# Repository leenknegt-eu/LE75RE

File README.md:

75 key, ortholinear, wired, 60% hot swappable keyboard for MX style (RE, RGB) and Gateron KS-33 low profile switches (LRE, LRGB).
Inspired by the Xiudi XD75RE which does not appear to be in regular production anymore.
All variants should be plate and case compatible with the XD75.
The legacy versions are ATMega32 powered and are pin for pin compatible with the XD75 and should be able to use the same firmware.
The LE75RGB variants have per-key RGB backlighting intended for use with SK6803MINI-E LED ICs.

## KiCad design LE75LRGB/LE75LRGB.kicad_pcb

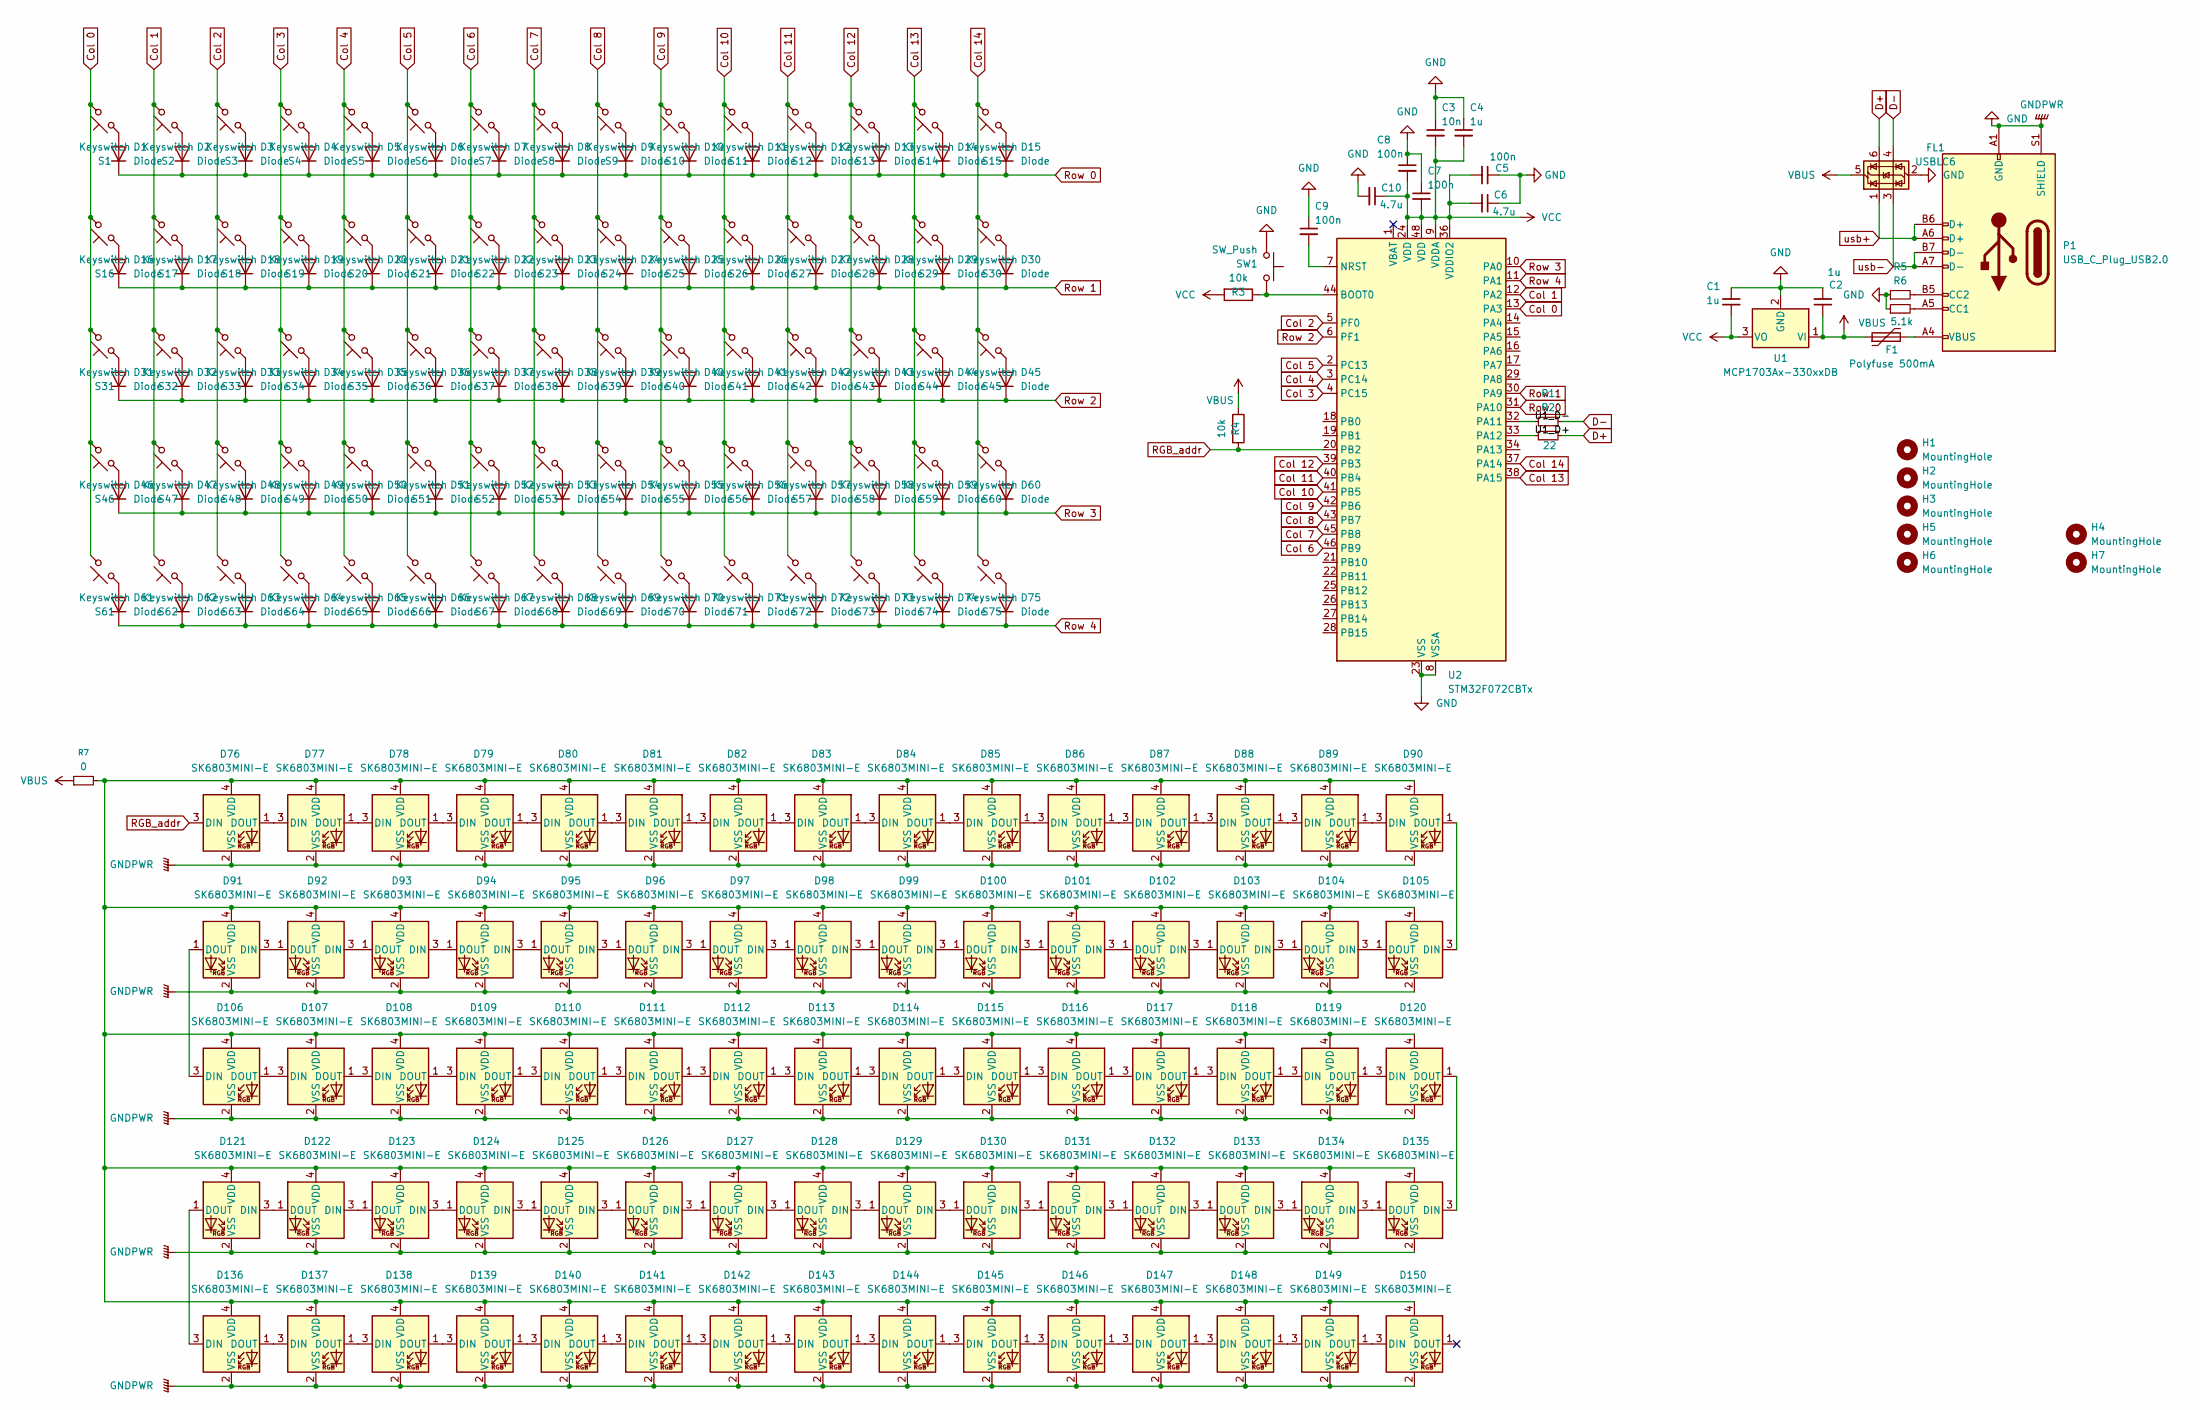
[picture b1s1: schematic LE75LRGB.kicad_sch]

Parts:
C1, C2, C4: 1u; C_0603_1608Metric
C3: 10n; C_0603_1608Metric
C5, C7, C8, C9: 100n; C_0603_1608Metric
C6, C10: 4.7u; C_0603_1608Metric
D1, D2, D3, D4, D5, D6, D7, D8, D9, D10, D11, D12, D13, D14, D15, D16, D17, D18, D19, D20, D21, D22, D23, D24, D25, D26, D27, D28, D29, D30, D31, D32, D33, D34, D35, D36, D37, D38, D39, D40, D41, D42, D43, D44, D45, D46, D47, D48, D49, D50, D51, D52, D53, D54, D55, D56, D57, D58, D59, D60, D61, D62, D63, D64, D65, D66, D67, D68, D69, D70, D71, D72, D73, D74, D75: Diode; D_0805_2012Metric
D76, D77, D78, D79, D80, D81, D82, D83, D84, D85, D86, D87, D88, D89, D90, D91, D92, D93, D94, D95, D96, D97, D98, D99, D100, D101, D102, D103, D104, D105, D106, D107, D108, D109, D110, D111, D112, D113, D114, D115, D116, D117, D118, D119, D120, D121, D122, D123, D124, D125, D126, D127, D128, D129, D130, D131, D132, D133, D134, D135, D136, D137, D138, D139, D140, D141, D142, D143, D144, D145, D146, D147, D148, D149, D150: SK6803MINI-E; SK6812-MINI-E
F1: Polyfuse 500mA; Fuse_1206_3216Metric
FL1: USBLC6; SOT-23-6; Manufacturer_Part_Number ECMF02-4CMX8; Mouser Part Number 511-ECMF02-4CMX8
H1, H2, H3, H5, H6: MountingHole; MountingHole_2.7mm_M2.5_ISO7380
H4, H7: MountingHole; MountingSlot_2.7mm_M2.5_ISO7380
P1: USB_C_Plug_USB2.0; USB_C_Receptacle_Palconn_UTC16-G
R1, R2: 22; R_0603_1608Metric
R3, R4: 10k; R_0603_1608Metric
R5, R6: 5.1k; R_0603_1608Metric
R7: 0; C_0603_1608Metric
S1, S2, S3, S4, S5, S6, S7, S8, S9, S10, S11, S12, S13, S14, S15, S16, S17, S18, S19, S20, S21, S22, S23, S24, S25, S26, S27, S28, S29, S30, S31, S32, S33, S34, S35, S36, S37, S38, S39, S40, S41, S42, S43, S44, S45, S46, S47, S48, S49, S50, S51, S52, S53, S54, S55, S56, S57, S58, S59, S60, S61, S62, S63, S64, S65, S66, S67, S68, S69, S70, S71, S72, S73, S74, S75: Keyswitch; Gateron-KS33-Hotswap-1U
SW1: SW_Push; SW_SPST_TL3342
U1: MCP1703Ax-330xxDB; SOT-23
U2: STM32F072CBTx; LQFP-48_7x7mm_P0.5mm

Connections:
/U1_D+: R2.1, U2.33 (PA12)
/U1_D-: R1.1, U2.32 (PA11)
Col 0: S1.2, S16.2, S31.2, S46.2, S61.2, U2.13 (PA3)
Col 1: S2.2, S17.2, S32.2, S47.2, S62.2, U2.12 (PA2)
Col 2: S3.2, S18.2, S33.2, S48.2, S63.2, U2.5 (PF0)
Col 3: S4.2, S19.2, S34.2, S49.2, S64.2, U2.4 (PC15)
Col 4: S5.2, S20.2, S35.2, S50.2, S65.2, U2.3 (PC14)
Col 5: S6.2, S21.2, S36.2, S51.2, S66.2, U2.2 (PC13)
Col 6: S7.2, S22.2, S37.2, S52.2, S67.2, U2.46 (PB9)
Col 7: S8.2, S23.2, S38.2, S53.2, S68.2, U2.45 (PB8)
Col 8: S9.2, S24.2, S39.2, S54.2, S69.2, U2.43 (PB7)
Col 9: S10.2, S25.2, S40.2, S55.2, S70.2, U2.42 (PB6)
Col 10: S11.2, S26.2, S41.2, S56.2, S71.2, U2.41 (PB5)
Col 11: S12.2, S27.2, S42.2, S57.2, S72.2, U2.40 (PB4)
Col 12: S13.2, S28.2, S43.2, S58.2, S73.2, U2.39 (PB3)
Col 13: S14.2, S29.2, S44.2, S59.2, S74.2, U2.38 (PA15)
Col 14: S15.2, S30.2, S45.2, S60.2, S75.2, U2.37 (PA14)
D+: FL1.6 (I/O1), R2.2
D-: FL1.4 (I/O2), R1.2
GND: C1.2, C2.2, C3.1, C4.1, C5.1, C6.1, C7.1, C8.1, C9.1, C10.2, D76.2 (VSS), D77.2 (VSS), D78.2 (VSS), D79.2 (VSS), D80.2 (VSS), D81.2 (VSS), D82.2 (VSS), D83.2 (VSS), D84.2 (VSS), D85.2 (VSS), D86.2 (VSS), D87.2 (VSS), D88.2 (VSS), D89.2 (VSS), D90.2 (VSS), D91.2 (VSS), D92.2 (VSS), D93.2 (VSS), D94.2 (VSS), D95.2 (VSS), D96.2 (VSS), D97.2 (VSS), D98.2 (VSS), D99.2 (VSS), D100.2 (VSS), D101.2 (VSS), D102.2 (VSS), D103.2 (VSS), D104.2 (VSS), D105.2 (VSS), D106.2 (VSS), D107.2 (VSS), D108.2 (VSS), D109.2 (VSS), D110.2 (VSS), D111.2 (VSS), D112.2 (VSS), D113.2 (VSS), D114.2 (VSS), D115.2 (VSS), D116.2 (VSS), D117.2 (VSS), D118.2 (VSS), D119.2 (VSS), D120.2 (VSS), D121.2 (VSS), D122.2 (VSS), D123.2 (VSS), D124.2 (VSS), D125.2 (VSS), D126.2 (VSS), D127.2 (VSS), D128.2 (VSS), D129.2 (VSS), D130.2 (VSS), D131.2 (VSS), D132.2 (VSS), D133.2 (VSS), D134.2 (VSS), D135.2 (VSS), D136.2 (VSS), D137.2 (VSS), D138.2 (VSS), D139.2 (VSS), D140.2 (VSS), D141.2 (VSS), D142.2 (VSS), D143.2 (VSS), D144.2 (VSS), D145.2 (VSS), D146.2 (VSS), D147.2 (VSS), D148.2 (VSS), D149.2 (VSS), D150.2 (VSS), FL1.2 (GND), P1.A1 (GND), P1.A12 (GND), P1.B1 (GND), P1.B12 (GND), P1.S1 (SHIELD), R5.1, R6.1, SW1.1, U1.2 (GND), U2.8 (VSSA), U2.23 (VSS), U2.35 (VSS), U2.47 (VSS)
unnamed: D1.2 (A), S1.1
unnamed: D2.2 (A), S2.1
unnamed: D3.2 (A), S3.1
unnamed: D4.2 (A), S4.1
unnamed: D5.2 (A), S5.1
unnamed: D6.2 (A), S6.1
unnamed: D7.2 (A), S7.1
unnamed: D8.2 (A), S8.1
unnamed: D9.2 (A), S9.1
unnamed: D10.2 (A), S10.1
unnamed: D11.2 (A), S11.1
unnamed: D12.2 (A), S12.1
unnamed: D13.2 (A), S13.1
unnamed: D14.2 (A), S14.1
unnamed: D15.2 (A), S15.1
unnamed: D16.2 (A), S16.1
unnamed: D17.2 (A), S17.1
unnamed: D18.2 (A), S18.1
unnamed: D19.2 (A), S19.1
unnamed: D20.2 (A), S20.1
unnamed: D21.2 (A), S21.1
unnamed: D22.2 (A), S22.1
unnamed: D23.2 (A), S23.1
unnamed: D24.2 (A), S24.1
unnamed: D25.2 (A), S25.1
unnamed: D26.2 (A), S26.1
unnamed: D27.2 (A), S27.1
unnamed: D28.2 (A), S28.1
unnamed: D29.2 (A), S29.1
unnamed: D30.2 (A), S30.1
unnamed: D31.2 (A), S31.1
unnamed: D32.2 (A), S32.1
unnamed: D33.2 (A), S33.1
unnamed: D34.2 (A), S34.1
unnamed: D35.2 (A), S35.1
unnamed: D36.2 (A), S36.1
unnamed: D37.2 (A), S37.1
unnamed: D38.2 (A), S38.1
unnamed: D39.2 (A), S39.1
unnamed: D40.2 (A), S40.1
unnamed: D41.2 (A), S41.1
unnamed: D42.2 (A), S42.1
unnamed: D43.2 (A), S43.1
unnamed: D44.2 (A), S44.1
unnamed: D45.2 (A), S45.1
unnamed: D46.2 (A), S46.1
unnamed: D47.2 (A), S47.1
unnamed: D48.2 (A), S48.1
unnamed: D49.2 (A), S49.1
unnamed: D50.2 (A), S50.1
unnamed: D51.2 (A), S51.1
unnamed: D52.2 (A), S52.1
unnamed: D53.2 (A), S53.1
unnamed: D54.2 (A), S54.1
unnamed: D55.2 (A), S55.1
unnamed: D56.2 (A), S56.1
unnamed: D57.2 (A), S57.1
unnamed: D58.2 (A), S58.1
unnamed: D59.2 (A), S59.1
unnamed: D60.2 (A), S60.1
unnamed: D61.2 (A), S61.1
unnamed: D62.2 (A), S62.1
unnamed: D63.2 (A), S63.1
unnamed: D64.2 (A), S64.1
unnamed: D65.2 (A), S65.1
unnamed: D66.2 (A), S66.1
unnamed: D67.2 (A), S67.1
unnamed: D68.2 (A), S68.1
unnamed: D69.2 (A), S69.1
unnamed: D70.2 (A), S70.1
unnamed: D71.2 (A), S71.1
unnamed: D72.2 (A), S72.1
unnamed: D73.2 (A), S73.1
unnamed: D74.2 (A), S74.1
unnamed: D75.2 (A), S75.1
unnamed: D76.1 (DOUT), D77.3 (DIN)
unnamed: D77.1 (DOUT), D78.3 (DIN)
unnamed: D78.1 (DOUT), D79.3 (DIN)
unnamed: D79.1 (DOUT), D80.3 (DIN)
unnamed: D80.1 (DOUT), D81.3 (DIN)
unnamed: D81.1 (DOUT), D82.3 (DIN)
unnamed: D82.1 (DOUT), D83.3 (DIN)
unnamed: D83.1 (DOUT), D84.3 (DIN)
unnamed: D84.1 (DOUT), D85.3 (DIN)
unnamed: D85.1 (DOUT), D86.3 (DIN)
unnamed: D86.1 (DOUT), D87.3 (DIN)
unnamed: D87.1 (DOUT), D88.3 (DIN)
unnamed: D88.1 (DOUT), D89.3 (DIN)
unnamed: D89.1 (DOUT), D90.3 (DIN)
unnamed: D91.3 (DIN), D92.1 (DOUT)
unnamed: D92.3 (DIN), D93.1 (DOUT)
unnamed: D93.3 (DIN), D94.1 (DOUT)
unnamed: D94.3 (DIN), D95.1 (DOUT)
unnamed: D95.3 (DIN), D96.1 (DOUT)
unnamed: D96.3 (DIN), D97.1 (DOUT)
unnamed: D97.3 (DIN), D98.1 (DOUT)
unnamed: D98.3 (DIN), D99.1 (DOUT)
unnamed: D100.3 (DIN), D101.1 (DOUT)
unnamed: D99.3 (DIN), D100.1 (DOUT)
unnamed: D76.4 (VDD), D77.4 (VDD), D78.4 (VDD), D79.4 (VDD), D80.4 (VDD), D81.4 (VDD), D82.4 (VDD), D83.4 (VDD), D84.4 (VDD), D85.4 (VDD), D86.4 (VDD), D87.4 (VDD), D88.4 (VDD), D89.4 (VDD), D90.4 (VDD), D91.4 (VDD), D92.4 (VDD), D93.4 (VDD), D94.4 (VDD), D95.4 (VDD), D96.4 (VDD), D97.4 (VDD), D98.4 (VDD), D99.4 (VDD), D100.4 (VDD), D101.4 (VDD), D102.4 (VDD), D103.4 (VDD), D104.4 (VDD), D105.4 (VDD), D106.4 (VDD), D107.4 (VDD), D108.4 (VDD), D109.4 (VDD), D110.4 (VDD), D111.4 (VDD), D112.4 (VDD), D113.4 (VDD), D114.4 (VDD), D115.4 (VDD), D116.4 (VDD), D117.4 (VDD), D118.4 (VDD), D119.4 (VDD), D120.4 (VDD), D121.4 (VDD), D122.4 (VDD), D123.4 (VDD), D124.4 (VDD), D125.4 (VDD), D126.4 (VDD), D127.4 (VDD), D128.4 (VDD), D129.4 (VDD), D130.4 (VDD), D131.4 (VDD), D132.4 (VDD), D133.4 (VDD), D134.4 (VDD), D135.4 (VDD), D136.4 (VDD), D137.4 (VDD), D138.4 (VDD), D139.4 (VDD), D140.4 (VDD), D141.4 (VDD), D142.4 (VDD), D143.4 (VDD), D144.4 (VDD), D145.4 (VDD), D146.4 (VDD), D147.4 (VDD), D148.4 (VDD), D149.4 (VDD), D150.4 (VDD), R7.2
unnamed: D101.3 (DIN), D102.1 (DOUT)
unnamed: D102.3 (DIN), D103.1 (DOUT)
unnamed: D103.3 (DIN), D104.1 (DOUT)
unnamed: D104.3 (DIN), D105.1 (DOUT)
unnamed: D90.1 (DOUT), D105.3 (DIN)
unnamed: D91.1 (DOUT), D106.3 (DIN)
unnamed: D106.1 (DOUT), D107.3 (DIN)
unnamed: D107.1 (DOUT), D108.3 (DIN)
unnamed: D108.1 (DOUT), D109.3 (DIN)
unnamed: D109.1 (DOUT), D110.3 (DIN)
unnamed: D110.1 (DOUT), D111.3 (DIN)
unnamed: D111.1 (DOUT), D112.3 (DIN)
unnamed: D112.1 (DOUT), D113.3 (DIN)
unnamed: D113.1 (DOUT), D114.3 (DIN)
unnamed: D114.1 (DOUT), D115.3 (DIN)
unnamed: D115.1 (DOUT), D116.3 (DIN)
unnamed: D116.1 (DOUT), D117.3 (DIN)
unnamed: D117.1 (DOUT), D118.3 (DIN)
unnamed: D118.1 (DOUT), D119.3 (DIN)
unnamed: D119.1 (DOUT), D120.3 (DIN)
unnamed: D120.1 (DOUT), D135.3 (DIN)
unnamed: D121.3 (DIN), D122.1 (DOUT)
unnamed: D121.1 (DOUT), D136.3 (DIN)
unnamed: D122.3 (DIN), D123.1 (DOUT)
unnamed: D123.3 (DIN), D124.1 (DOUT)
unnamed: D124.3 (DIN), D125.1 (DOUT)
unnamed: D125.3 (DIN), D126.1 (DOUT)
unnamed: D126.3 (DIN), D127.1 (DOUT)
unnamed: D127.3 (DIN), D128.1 (DOUT)
unnamed: D128.3 (DIN), D129.1 (DOUT)
unnamed: D129.3 (DIN), D130.1 (DOUT)
unnamed: D130.3 (DIN), D131.1 (DOUT)
unnamed: D131.3 (DIN), D132.1 (DOUT)
unnamed: D132.3 (DIN), D133.1 (DOUT)
unnamed: D133.3 (DIN), D134.1 (DOUT)
unnamed: D134.3 (DIN), D135.1 (DOUT)
unnamed: D136.1 (DOUT), D137.3 (DIN)
unnamed: D137.1 (DOUT), D138.3 (DIN)
unnamed: D138.1 (DOUT), D139.3 (DIN)
unnamed: D139.1 (DOUT), D140.3 (DIN)
unnamed: D140.1 (DOUT), D141.3 (DIN)
unnamed: D141.1 (DOUT), D142.3 (DIN)
unnamed: D142.1 (DOUT), D143.3 (DIN)
unnamed: D143.1 (DOUT), D144.3 (DIN)
unnamed: D144.1 (DOUT), D145.3 (DIN)
unnamed: D145.1 (DOUT), D146.3 (DIN)
unnamed: D146.1 (DOUT), D147.3 (DIN)
unnamed: D147.1 (DOUT), D148.3 (DIN)
unnamed: D148.1 (DOUT), D149.3 (DIN)
unnamed: D149.1 (DOUT), D150.3 (DIN)
unnamed: F1.2, P1.A4 (VBUS), P1.A9 (VBUS), P1.B4 (VBUS), P1.B9 (VBUS)
unnamed: P1.A5 (CC1), R6.2
unnamed: P1.B5 (CC2), R5.2
unnamed: R3.1, SW1.2, U2.44 (BOOT0)
unnamed: C9.2, U2.7 (NRST)
RGB_addr: D76.3 (DIN), R4.2, U2.20 (PB2)
Row 0: D1.1 (K), D2.1 (K), D3.1 (K), D4.1 (K), D5.1 (K), D6.1 (K), D7.1 (K), D8.1 (K), D9.1 (K), D10.1 (K), D11.1 (K), D12.1 (K), D13.1 (K), D14.1 (K), D15.1 (K), U2.31 (PA10)
Row 1: D16.1 (K), D17.1 (K), D18.1 (K), D19.1 (K), D20.1 (K), D21.1 (K), D22.1 (K), D23.1 (K), D24.1 (K), D25.1 (K), D26.1 (K), D27.1 (K), D28.1 (K), D29.1 (K), D30.1 (K), U2.30 (PA9)
Row 2: D31.1 (K), D32.1 (K), D33.1 (K), D34.1 (K), D35.1 (K), D36.1 (K), D37.1 (K), D38.1 (K), D39.1 (K), D40.1 (K), D41.1 (K), D42.1 (K), D43.1 (K), D44.1 (K), D45.1 (K), U2.6 (PF1)
Row 3: D46.1 (K), D47.1 (K), D48.1 (K), D49.1 (K), D50.1 (K), D51.1 (K), D52.1 (K), D53.1 (K), D54.1 (K), D55.1 (K), D56.1 (K), D57.1 (K), D58.1 (K), D59.1 (K), D60.1 (K), U2.10 (PA0)
Row 4: D61.1 (K), D62.1 (K), D63.1 (K), D64.1 (K), D65.1 (K), D66.1 (K), D67.1 (K), D68.1 (K), D69.1 (K), D70.1 (K), D71.1 (K), D72.1 (K), D73.1 (K), D74.1 (K), D75.1 (K), U2.11 (PA1)
VBUS: C2.1, F1.1, FL1.5 (VBUS), R4.1, R7.1, U1.1 (VI)
VCC: C1.1, C3.2, C4.2, C5.2, C6.2, C7.2, C8.2, C10.1, R3.2, U1.3 (VO), U2.9 (VDDA), U2.24 (VDD), U2.36 (VDDIO2), U2.48 (VDD)
usb+: FL1.1 (I/O1), P1.A6 (D+), P1.B6 (D+)
usb-: FL1.3 (I/O2), P1.A7 (D-), P1.B7 (D-)

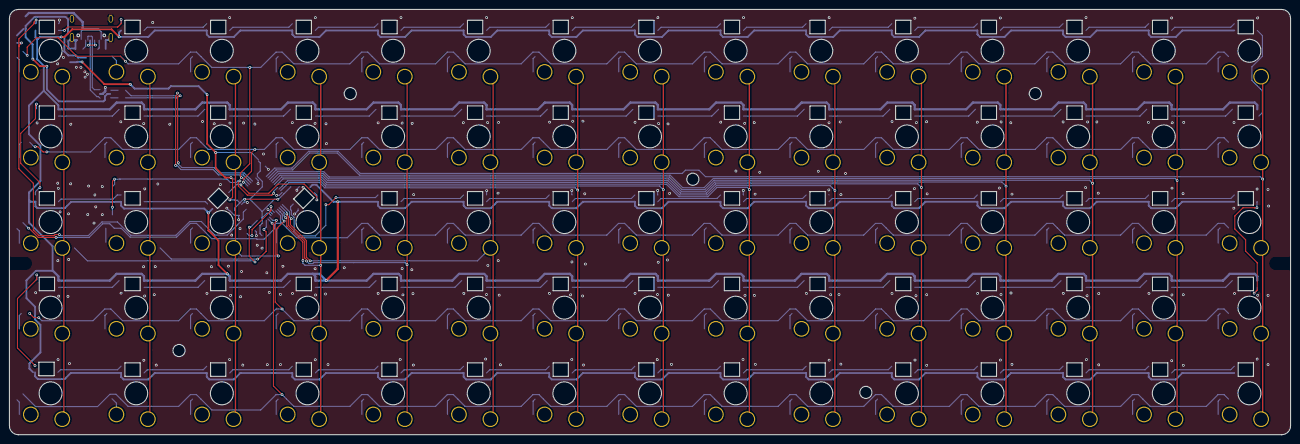
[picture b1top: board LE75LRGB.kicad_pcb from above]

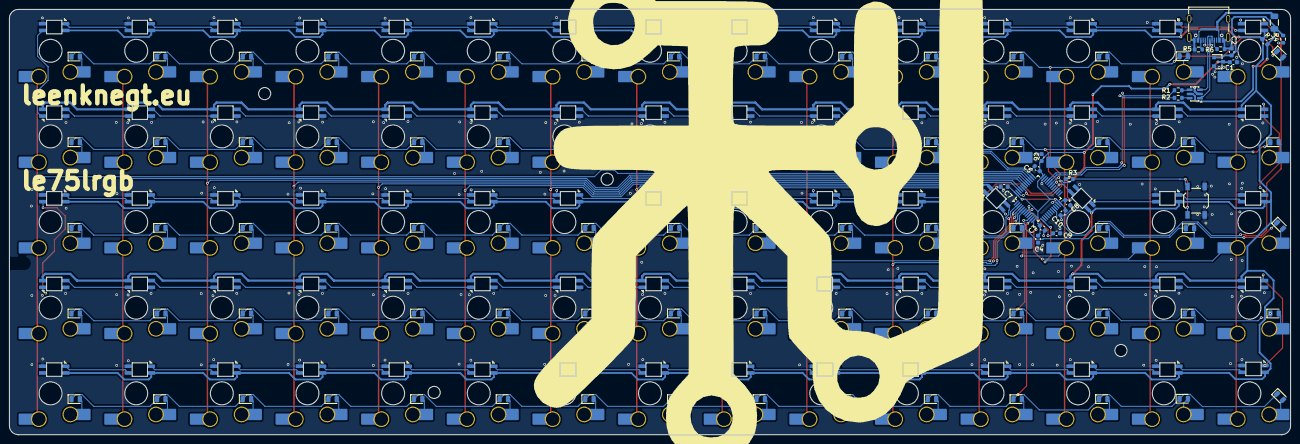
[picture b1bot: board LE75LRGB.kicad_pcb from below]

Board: 2 copper layers, 285.0 x 94.6 mm, 255 parts (248 on the bottom side), 185 nets.

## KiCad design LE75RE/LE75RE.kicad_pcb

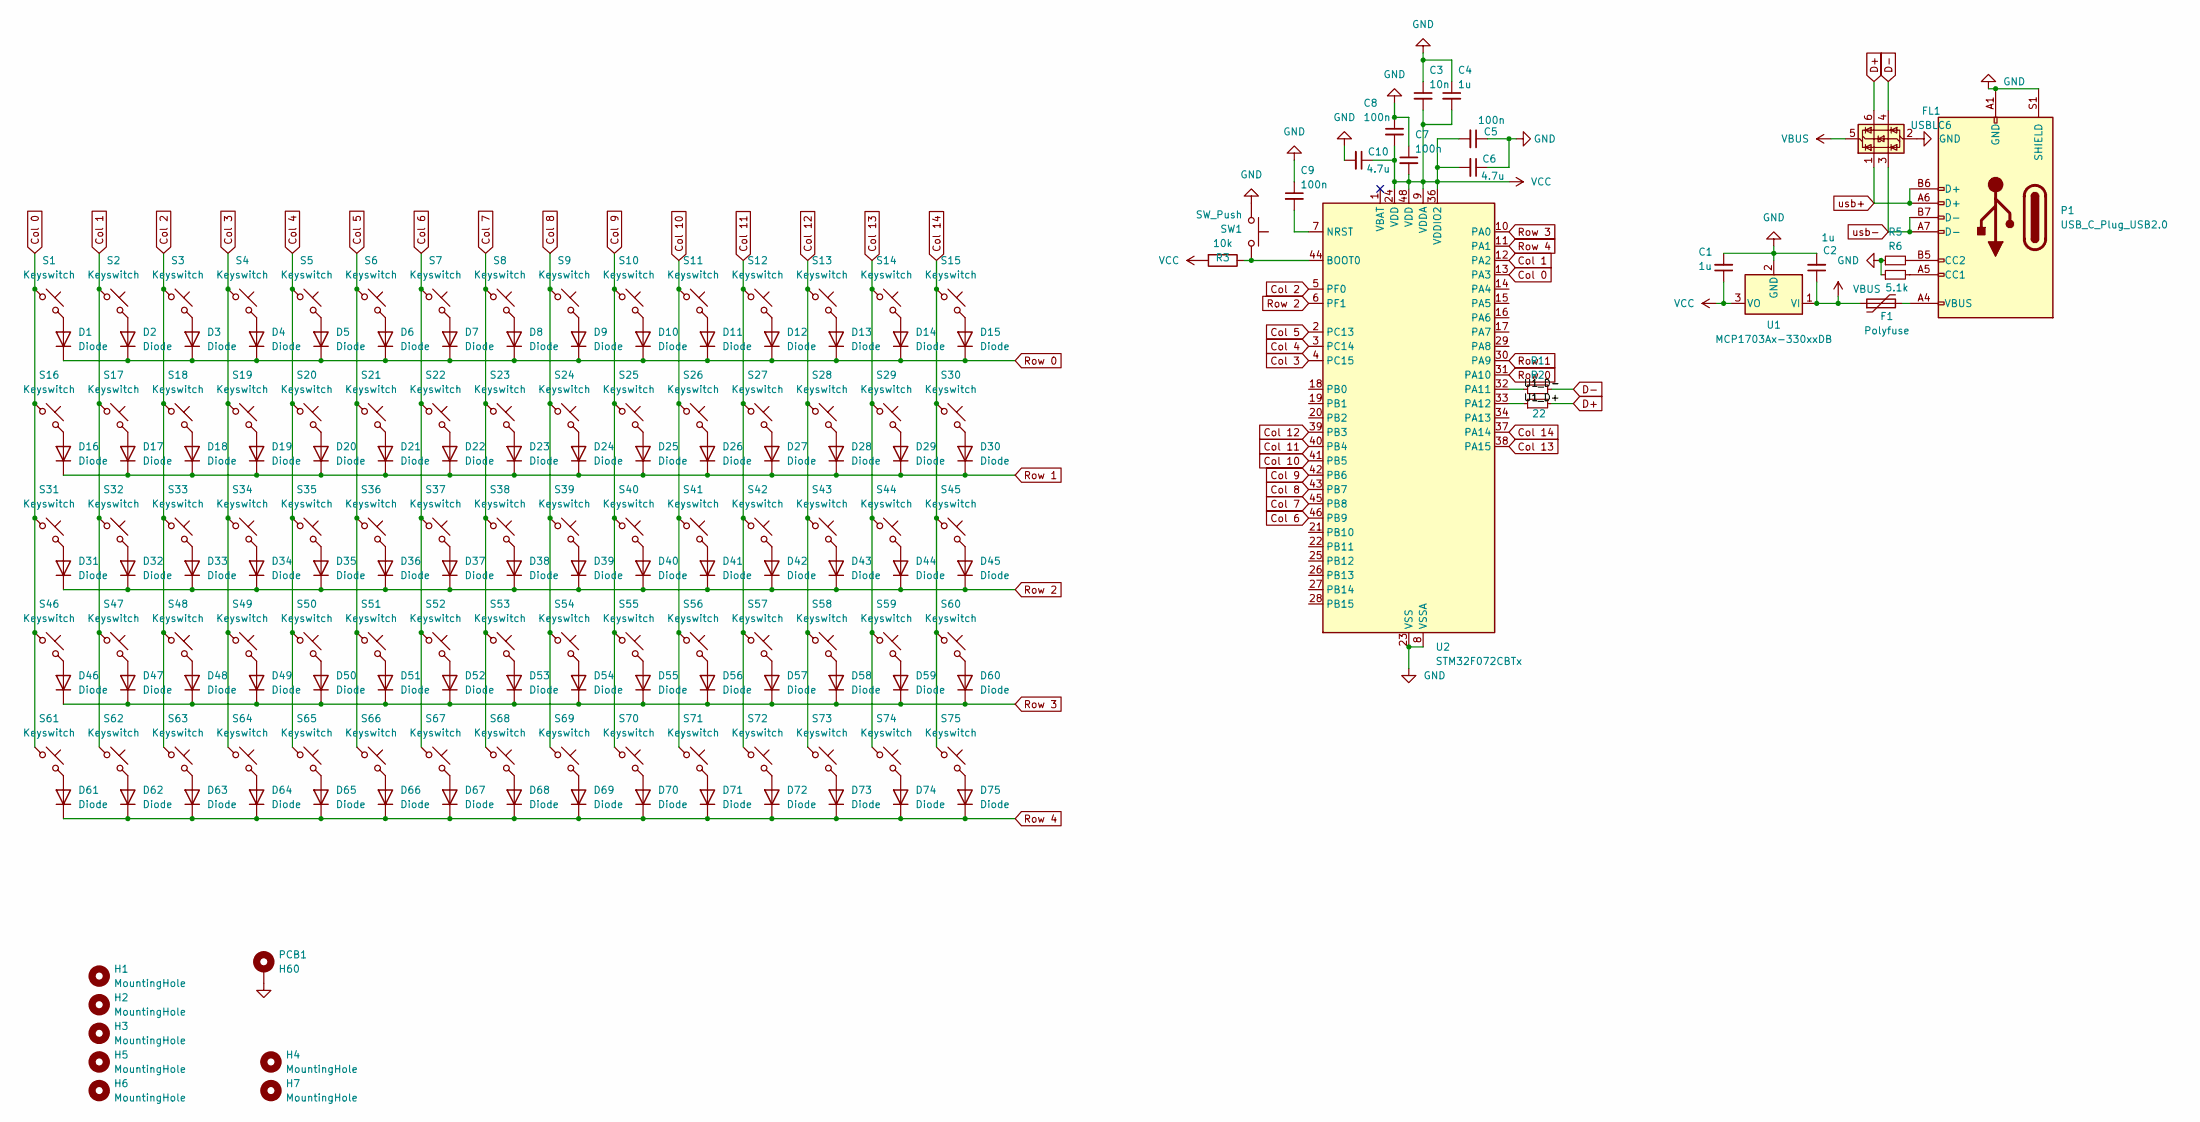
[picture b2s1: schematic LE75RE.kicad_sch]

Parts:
C1, C2, C4: 1u; C_0603_1608Metric
C3: 10n; C_0603_1608Metric
C5, C7, C8, C9: 100n; C_0603_1608Metric
C6, C10: 4.7u; C_0603_1608Metric
D1, D2, D3, D4, D5, D6, D7, D8, D9, D10, D11, D12, D13, D14, D15, D16, D17, D18, D19, D20, D21, D22, D23, D24, D25, D26, D27, D28, D29, D30, D31, D32, D33, D34, D35, D36, D37, D38, D39, D40, D41, D42, D43, D44, D45, D46, D47, D48, D49, D50, D51, D52, D53, D54, D55, D56, D57, D58, D59, D60, D61, D62, D63, D64, D65, D66, D67, D68, D69, D70, D71, D72, D73, D74, D75: Diode; D_0805_2012Metric
F1: Polyfuse; Fuse_1206_3216Metric
FL1: USBLC6; SOT-23-6; Manufacturer_Part_Number ECMF02-4CMX8; Mouser Part Number 511-ECMF02-4CMX8
H1, H2, H3, H5, H6: MountingHole; MountingHole_2.7mm_M2.5_ISO7380
H4, H7: MountingHole; MountingSlot_2.7mm_M2.5_ISO7380
P1: USB_C_Plug_USB2.0; USB_C_Receptacle_Palconn_UTC16-G
PCB1: H60
R1, R2: 22; R_0603_1608Metric
R3: 10k; R_0603_1608Metric
R5, R6: 5.1k; R_0603_1608Metric
S1, S2, S3, S4, S5, S6, S7, S8, S9, S10, S11, S12, S13, S14, S15, S16, S17, S18, S19, S20, S21, S22, S23, S24, S25, S26, S27, S28, S29, S30, S31, S32, S33, S34, S35, S36, S37, S38, S39, S40, S41, S42, S43, S44, S45, S46, S47, S48, S49, S50, S51, S52, S53, S54, S55, S56, S57, S58, S59, S60, S61, S62, S63, S64, S65, S66, S67, S68, S69, S70, S71, S72, S73, S74, S75: Keyswitch; SW_Hotswap_Kailh_MX_Plated
SW1: SW_Push; SW_SPST_TL3342
U1: MCP1703Ax-330xxDB; SOT-223-3_TabPin2
U2: STM32F072CBTx; LQFP-48_7x7mm_P0.5mm

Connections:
/U1_D+: R2.1, U2.33 (PA12)
/U1_D-: R1.1, U2.32 (PA11)
Col 0: S1.1, S16.1, S31.1, S46.1, S61.1, U2.13 (PA3)
Col 1: S2.1, S17.1, S32.1, S47.1, S62.1, U2.12 (PA2)
Col 2: S3.1, S18.1, S33.1, S48.1, S63.1, U2.5 (PF0)
Col 3: S4.1, S19.1, S34.1, S49.1, S64.1, U2.4 (PC15)
Col 4: S5.1, S20.1, S35.1, S50.1, S65.1, U2.3 (PC14)
Col 5: S6.1, S21.1, S36.1, S51.1, S66.1, U2.2 (PC13)
Col 6: S7.1, S22.1, S37.1, S52.1, S67.1, U2.46 (PB9)
Col 7: S8.1, S23.1, S38.1, S53.1, S68.1, U2.45 (PB8)
Col 8: S9.1, S24.1, S39.1, S54.1, S69.1, U2.43 (PB7)
Col 9: S10.1, S25.1, S40.1, S55.1, S70.1, U2.42 (PB6)
Col 10: S11.1, S26.1, S41.1, S56.1, S71.1, U2.41 (PB5)
Col 11: S12.1, S27.1, S42.1, S57.1, S72.1, U2.40 (PB4)
Col 12: S13.1, S28.1, S43.1, S58.1, S73.1, U2.39 (PB3)
Col 13: S14.1, S29.1, S44.1, S59.1, S74.1, U2.38 (PA15)
Col 14: S15.1, S30.1, S45.1, S60.1, S75.1, U2.37 (PA14)
D+: FL1.6 (I/O1), R2.2
D-: FL1.4 (I/O2), R1.2
GND: C1.2, C2.2, C3.1, C4.1, C5.1, C6.1, C7.1, C8.1, C9.1, C10.2, FL1.2 (GND), P1.A1 (GND), P1.A12 (GND), P1.B1 (GND), P1.B12 (GND), P1.S1 (SHIELD), PCB1.1, R5.1, R6.1, SW1.1, U1.2 (GND), U2.8 (VSSA), U2.23 (VSS), U2.35 (VSS), U2.47 (VSS)
unnamed: D1.2 (A), S1.2
unnamed: D2.2 (A), S2.2
unnamed: D3.2 (A), S3.2
unnamed: D4.2 (A), S4.2
unnamed: D5.2 (A), S5.2
unnamed: D6.2 (A), S6.2
unnamed: D7.2 (A), S7.2
unnamed: D8.2 (A), S8.2
unnamed: D9.2 (A), S9.2
unnamed: D10.2 (A), S10.2
unnamed: D11.2 (A), S11.2
unnamed: D12.2 (A), S12.2
unnamed: D13.2 (A), S13.2
unnamed: D14.2 (A), S14.2
unnamed: D15.2 (A), S15.2
unnamed: D16.2 (A), S16.2
unnamed: D17.2 (A), S17.2
unnamed: D18.2 (A), S18.2
unnamed: D19.2 (A), S19.2
unnamed: D20.2 (A), S20.2
unnamed: D21.2 (A), S21.2
unnamed: D22.2 (A), S22.2
unnamed: D23.2 (A), S23.2
unnamed: D24.2 (A), S24.2
unnamed: D25.2 (A), S25.2
unnamed: D26.2 (A), S26.2
unnamed: D27.2 (A), S27.2
unnamed: D28.2 (A), S28.2
unnamed: D29.2 (A), S29.2
unnamed: D30.2 (A), S30.2
unnamed: D31.2 (A), S31.2
unnamed: D32.2 (A), S32.2
unnamed: D33.2 (A), S33.2
unnamed: D34.2 (A), S34.2
unnamed: D35.2 (A), S35.2
unnamed: D36.2 (A), S36.2
unnamed: D37.2 (A), S37.2
unnamed: D38.2 (A), S38.2
unnamed: D39.2 (A), S39.2
unnamed: D40.2 (A), S40.2
unnamed: D41.2 (A), S41.2
unnamed: D42.2 (A), S42.2
unnamed: D43.2 (A), S43.2
unnamed: D44.2 (A), S44.2
unnamed: D45.2 (A), S45.2
unnamed: D46.2 (A), S46.2
unnamed: D47.2 (A), S47.2
unnamed: D48.2 (A), S48.2
unnamed: D49.2 (A), S49.2
unnamed: D50.2 (A), S50.2
unnamed: D51.2 (A), S51.2
unnamed: D52.2 (A), S52.2
unnamed: D53.2 (A), S53.2
unnamed: D54.2 (A), S54.2
unnamed: D55.2 (A), S55.2
unnamed: D56.2 (A), S56.2
unnamed: D57.2 (A), S57.2
unnamed: D58.2 (A), S58.2
unnamed: D59.2 (A), S59.2
unnamed: D60.2 (A), S60.2
unnamed: D61.2 (A), S61.2
unnamed: D62.2 (A), S62.2
unnamed: D63.2 (A), S63.2
unnamed: D64.2 (A), S64.2
unnamed: D65.2 (A), S65.2
unnamed: D66.2 (A), S66.2
unnamed: D67.2 (A), S67.2
unnamed: D68.2 (A), S68.2
unnamed: D69.2 (A), S69.2
unnamed: D70.2 (A), S70.2
unnamed: D71.2 (A), S71.2
unnamed: D72.2 (A), S72.2
unnamed: D73.2 (A), S73.2
unnamed: D74.2 (A), S74.2
unnamed: D75.2 (A), S75.2
unnamed: F1.2, P1.A4 (VBUS), P1.A9 (VBUS), P1.B4 (VBUS), P1.B9 (VBUS)
unnamed: P1.A5 (CC1), R6.2
unnamed: P1.B5 (CC2), R5.2
unnamed: R3.1, SW1.2, U2.44 (BOOT0)
unnamed: C9.2, U2.7 (NRST)
Row 0: D1.1 (K), D2.1 (K), D3.1 (K), D4.1 (K), D5.1 (K), D6.1 (K), D7.1 (K), D8.1 (K), D9.1 (K), D10.1 (K), D11.1 (K), D12.1 (K), D13.1 (K), D14.1 (K), D15.1 (K), U2.31 (PA10)
Row 1: D16.1 (K), D17.1 (K), D18.1 (K), D19.1 (K), D20.1 (K), D21.1 (K), D22.1 (K), D23.1 (K), D24.1 (K), D25.1 (K), D26.1 (K), D27.1 (K), D28.1 (K), D29.1 (K), D30.1 (K), U2.30 (PA9)
Row 2: D31.1 (K), D32.1 (K), D33.1 (K), D34.1 (K), D35.1 (K), D36.1 (K), D37.1 (K), D38.1 (K), D39.1 (K), D40.1 (K), D41.1 (K), D42.1 (K), D43.1 (K), D44.1 (K), D45.1 (K), U2.6 (PF1)
Row 3: D46.1 (K), D47.1 (K), D48.1 (K), D49.1 (K), D50.1 (K), D51.1 (K), D52.1 (K), D53.1 (K), D54.1 (K), D55.1 (K), D56.1 (K), D57.1 (K), D58.1 (K), D59.1 (K), D60.1 (K), U2.10 (PA0)
Row 4: D61.1 (K), D62.1 (K), D63.1 (K), D64.1 (K), D65.1 (K), D66.1 (K), D67.1 (K), D68.1 (K), D69.1 (K), D70.1 (K), D71.1 (K), D72.1 (K), D73.1 (K), D74.1 (K), D75.1 (K), U2.11 (PA1)
VBUS: C2.1, F1.1, FL1.5 (VBUS), U1.1 (VI)
VCC: C1.1, C3.2, C4.2, C5.2, C6.2, C7.2, C8.2, C10.1, R3.2, U1.3 (VO), U2.9 (VDDA), U2.24 (VDD), U2.36 (VDDIO2), U2.48 (VDD)
usb+: FL1.1 (I/O1), P1.A6 (D+), P1.B6 (D+)
usb-: FL1.3 (I/O2), P1.A7 (D-), P1.B7 (D-)

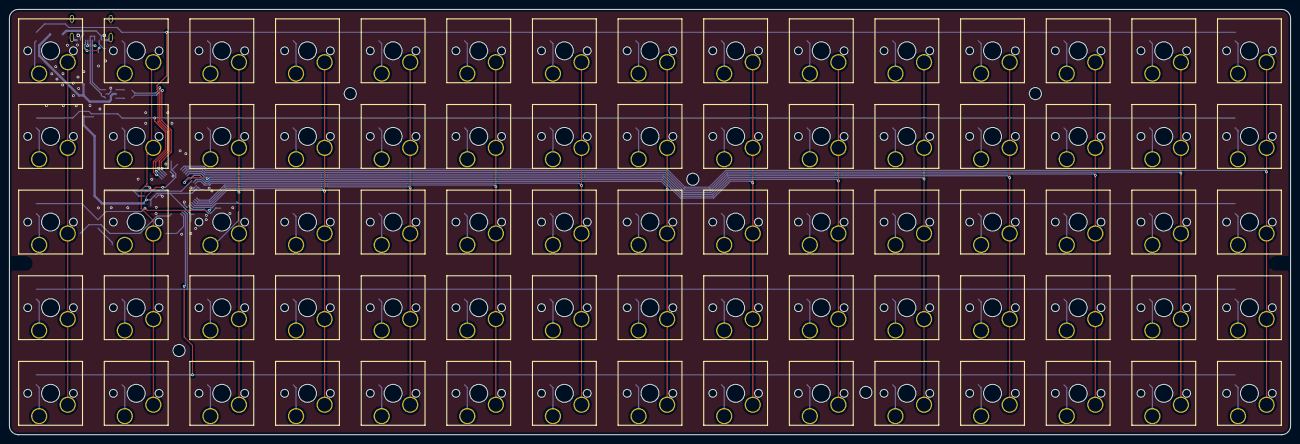
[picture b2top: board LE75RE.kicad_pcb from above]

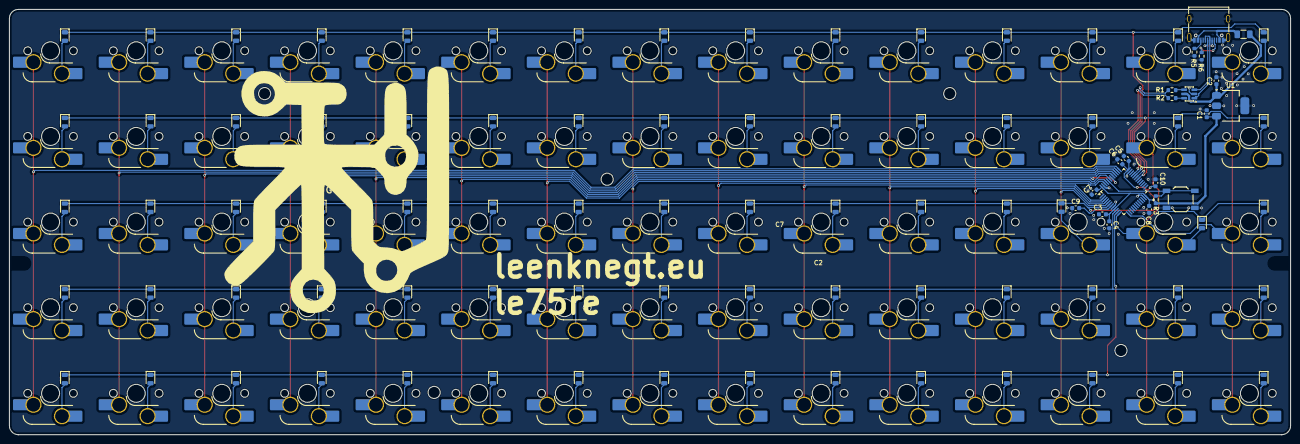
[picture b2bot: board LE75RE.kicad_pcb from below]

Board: 2 copper layers, 285.0 x 94.6 mm, 178 parts (96 on the bottom side), 109 nets.

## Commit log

2026-04-10 Low profile variant
    Small fixes, added LP variant
2026-04-11 Many changes
2026-04-12 Update README.md
    mention RGB variants
2026-04-13 Added RGB variants/changed a lot
2026-04-13 rounded corners
2026-04-14 updated RGB variants
